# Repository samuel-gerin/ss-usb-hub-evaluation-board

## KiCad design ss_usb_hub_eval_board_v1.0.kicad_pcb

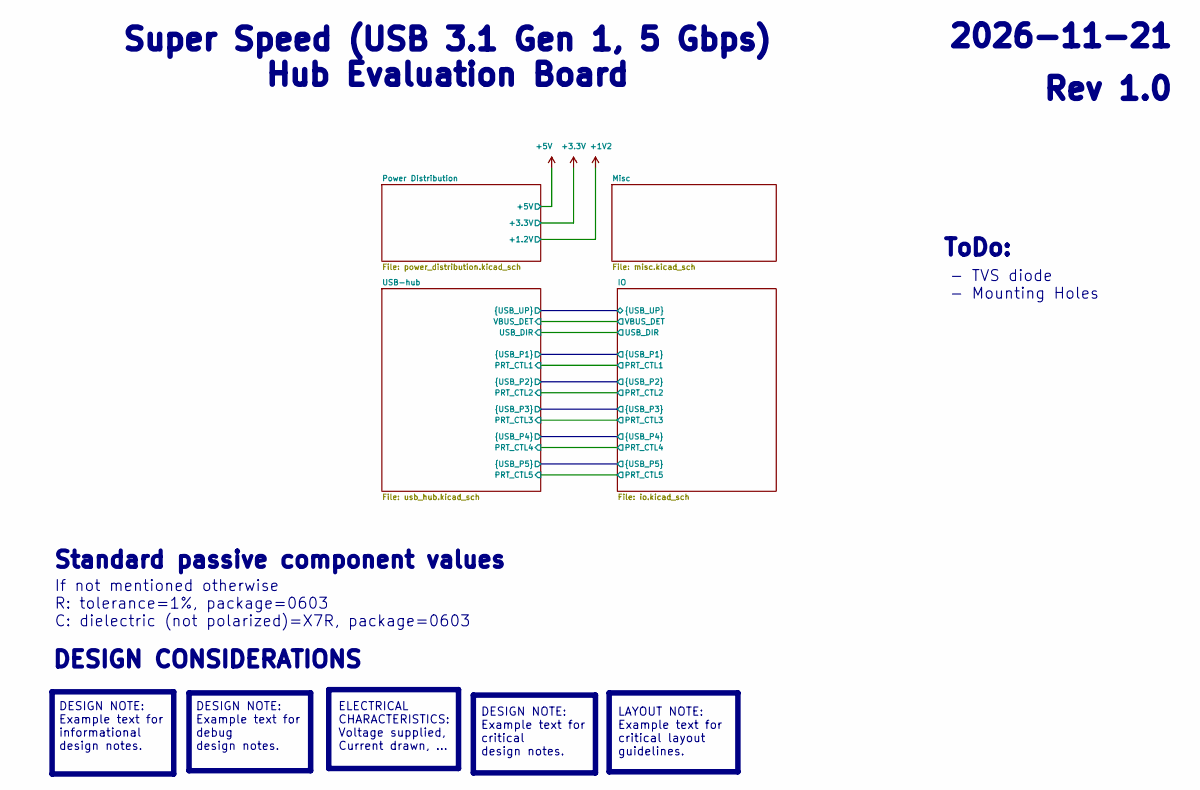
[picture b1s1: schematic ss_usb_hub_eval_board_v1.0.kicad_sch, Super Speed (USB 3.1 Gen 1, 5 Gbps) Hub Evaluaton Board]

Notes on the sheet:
If not mentioned otherwise R: tolerance=1%, package=0603 C: dielectric (not polarized)=X7R, package=0603
- TVS diode - Mounting Holes
DESIGN NOTE: Example text for critical design notes.
2026-11-21
Standard passive component values
Rev 1.0
DESIGN NOTE: Example text for informational design notes.
LAYOUT NOTE: Example text for critical layout guidelines.
DESIGN NOTE: Example text for debug design notes.
ELECTRICAL CHARACTERISTICS: Voltage supplied, Current drawn, ...
ToDo:
Super Speed (USB 3.1 Gen 1, 5 Gbps) Hub Evaluation Board
DESIGN CONSIDERATIONS

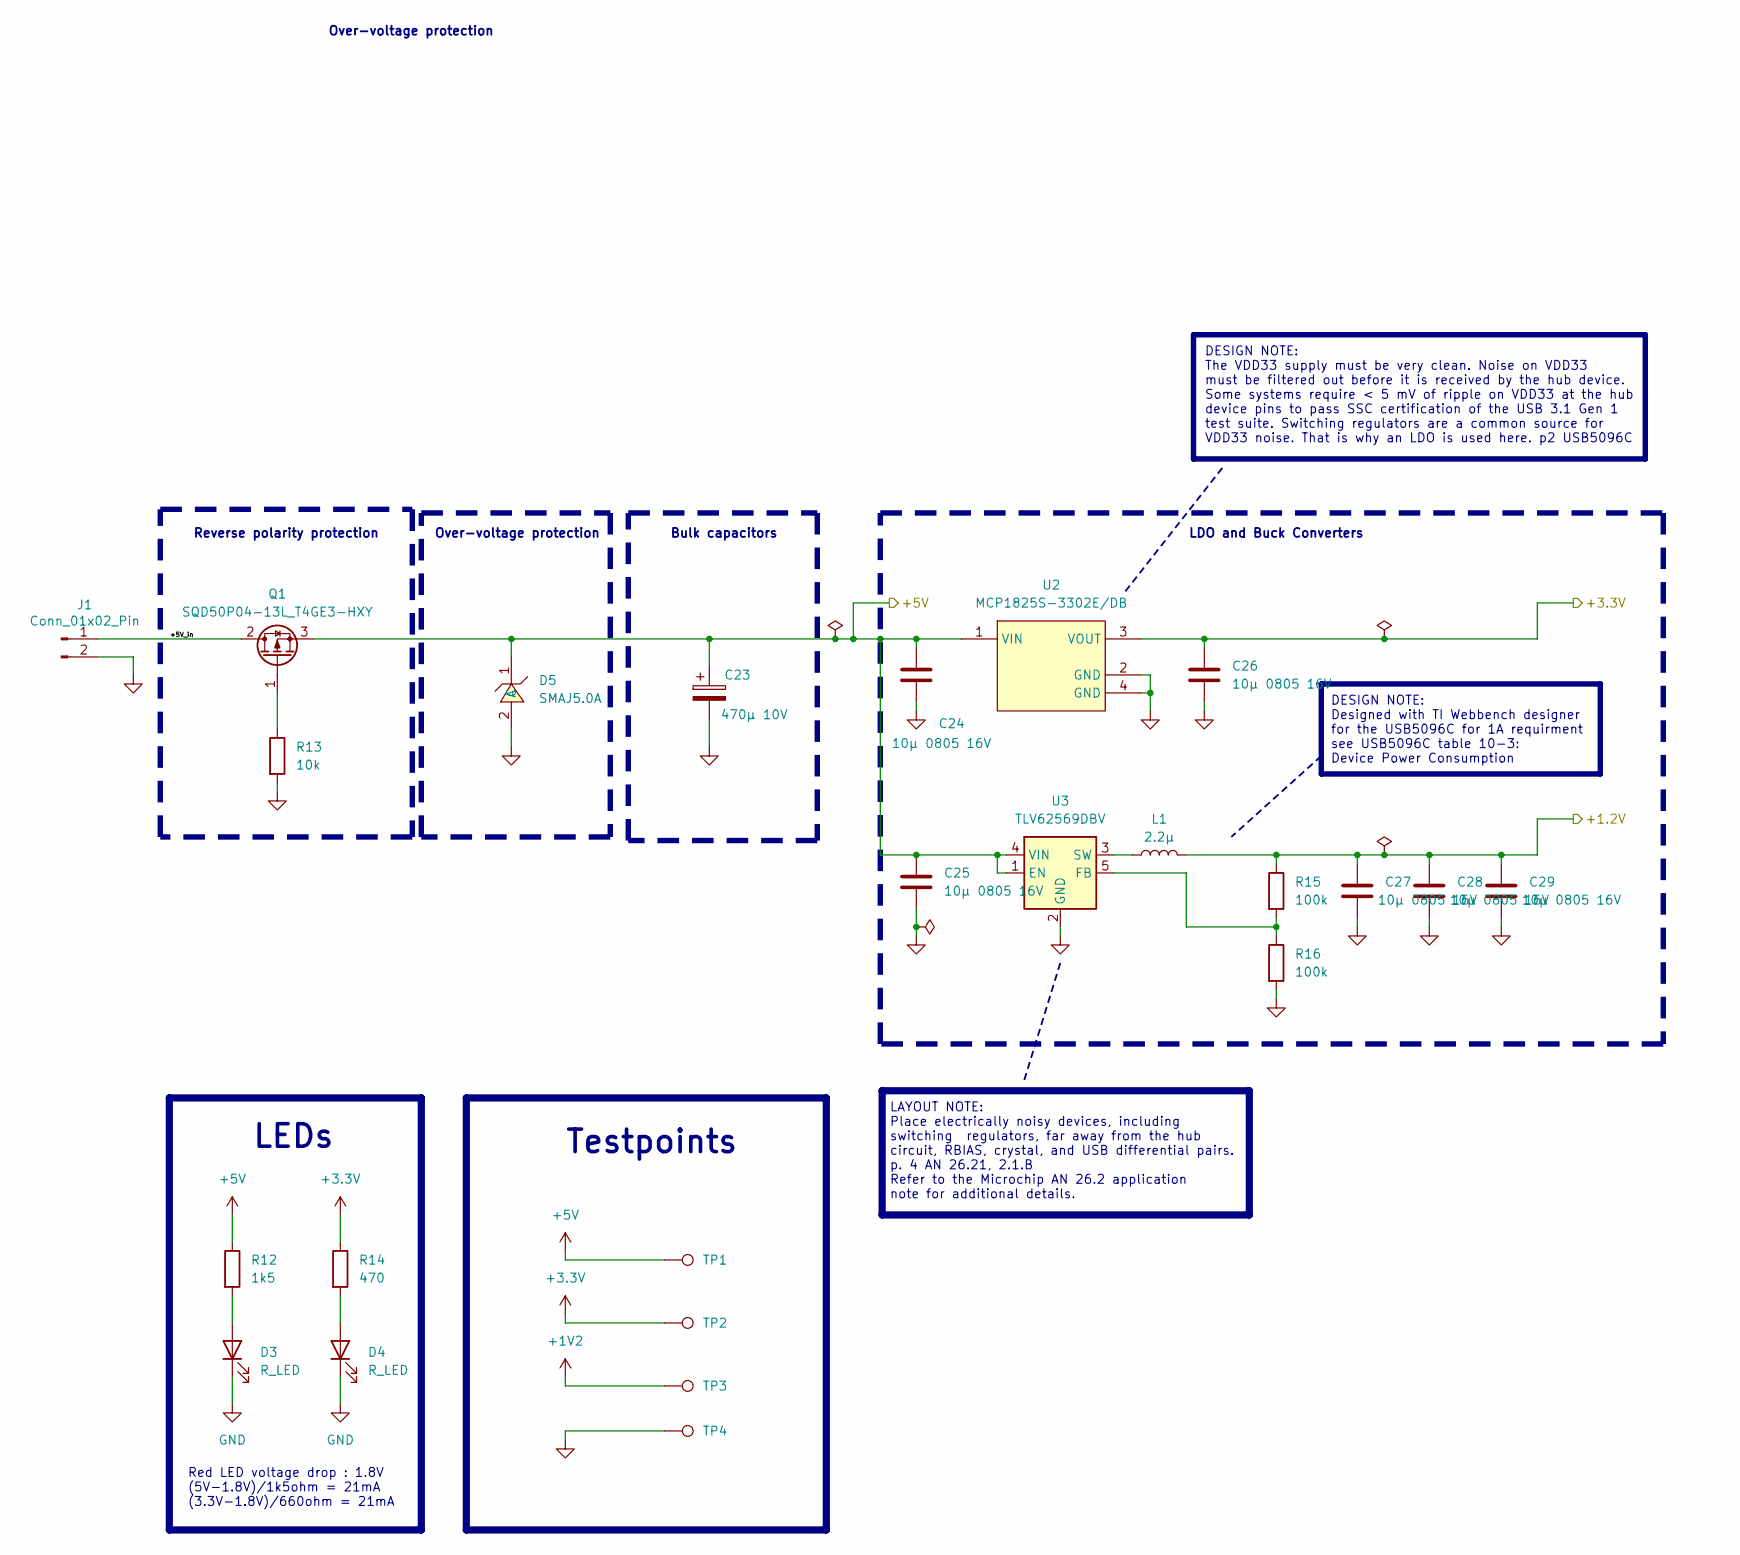
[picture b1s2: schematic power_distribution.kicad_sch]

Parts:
C23: 470µ 10V; CP_Elec_10x12.5; LCSC C22469994
C24, C25, C26, C27, C28, C29: 10µ 0805 16V; C_0805_2012Metric; LCSC C1713
D3, D4: R_LED; LED_0603_1608Metric; LCSC C2286
D5: SMAJ5.0A; SMA_L4.3-W2.6-LS5.2-RD; MPN SMAJ5.0A; LCSC Part C83329
J1: Conn_01x02_Pin; TerminalBlock_Phoenix_MKDS-1,5-2-5.08_1x02_P5.08mm_Horizont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
L1: 2.2µ; IND-SMD_L4.0-W4.0-A; LCSC C3151182
Q1: SQD50P04-13L_T4GE3-HXY; TO-252-2; LCSC C49256455
R12: 1k5; R_0603_1608Metric; LCSC C22843
R13: 10k; R_0805_2012Metric; LCSC C17414
R14: 470; R_0603_1608Metric; LCSC C23179
R15, R16: 100k; R_0603_1608Metric; LCSC C25803
TP1, TP2, TP3: TestPoint; TH_BD3.2-D2.0; LCSC C238122
TP4: TestPoint; TH_BD3.2-D2.0; LCSC C5199900
U2: MCP1825S-3302E/DB; SOT-223-3_L6.5-W3.4-P2.30-LS7.0-BR; MPN MCP1825S-3302E/DB; LCSC Part C148031
U3: TLV62569DBV; SOT-23-5; LCSC C141836

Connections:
+1V2: C27.1, C28.1, C29.1, L1.2, R15.1, TP3.1 (1_1); also elsewhere on the board
+3.3V: C26.1, R14.1, TP2.1 (1_1), U2.3 (VOUT); also elsewhere on the board
+5V: C23.1, C24.1, C25.1, D5.1 (C), Q1.3 (S), R12.1, TP1.1 (1_1), U2.1 (VIN), U3.1 (EN), U3.4 (VIN); also elsewhere on the board
/Power Distribution/+5V_in: J1.1, Q1.2 (D)
GND: C23.2, C24.2, C25.2, C26.2, C27.2, C28.2, C29.2, D3.1 (K), D4.1 (K), D5.2 (A), J1.2, R13.2, R16.2, TP4.1 (1_1), U2.2 (GND), U2.4 (GND), U3.2 (GND); also elsewhere on the board
unnamed: D3.2 (A), R12.2
unnamed: D4.2 (A), R14.2
unnamed: Q1.1 (G), R13.1
unnamed: R15.2, R16.1, U3.5 (FB)
unnamed: L1.1, U3.3 (SW)

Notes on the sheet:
Red LED voltage drop : 1.8V (5V-1.8V)/1k5ohm = 21mA (3.3V-1.8V)/660ohm = 21mA
Reverse polarity protection
LDO and Buck Converters
Over-voltage protection
Testpoints
Bulk capacitors
DESIGN NOTE: Designed with TI Webbench designer for the USB5096C for 1A requirment see USB5096C table 10-3: Device Power Consumption
LAYOUT NOTE: Place electrically noisy devices, including switching regulators, far away from the hub circuit, RBIAS, crystal, and USB differential pairs. p. 4 AN 26.21, 2.1.B Refer to the Microchip AN 26.2 application note for additional details.
DESIGN NOTE: The VDD33 supply must be very clean. Noise on VDD33 must be filtered out before it is received by the hub device. Some systems require < 5 mV of ripple on VDD33 at the hub device pins to pass SSC certification of the USB 3.1 Gen 1 test suite. Switching regulators are a common source fo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
LEDs

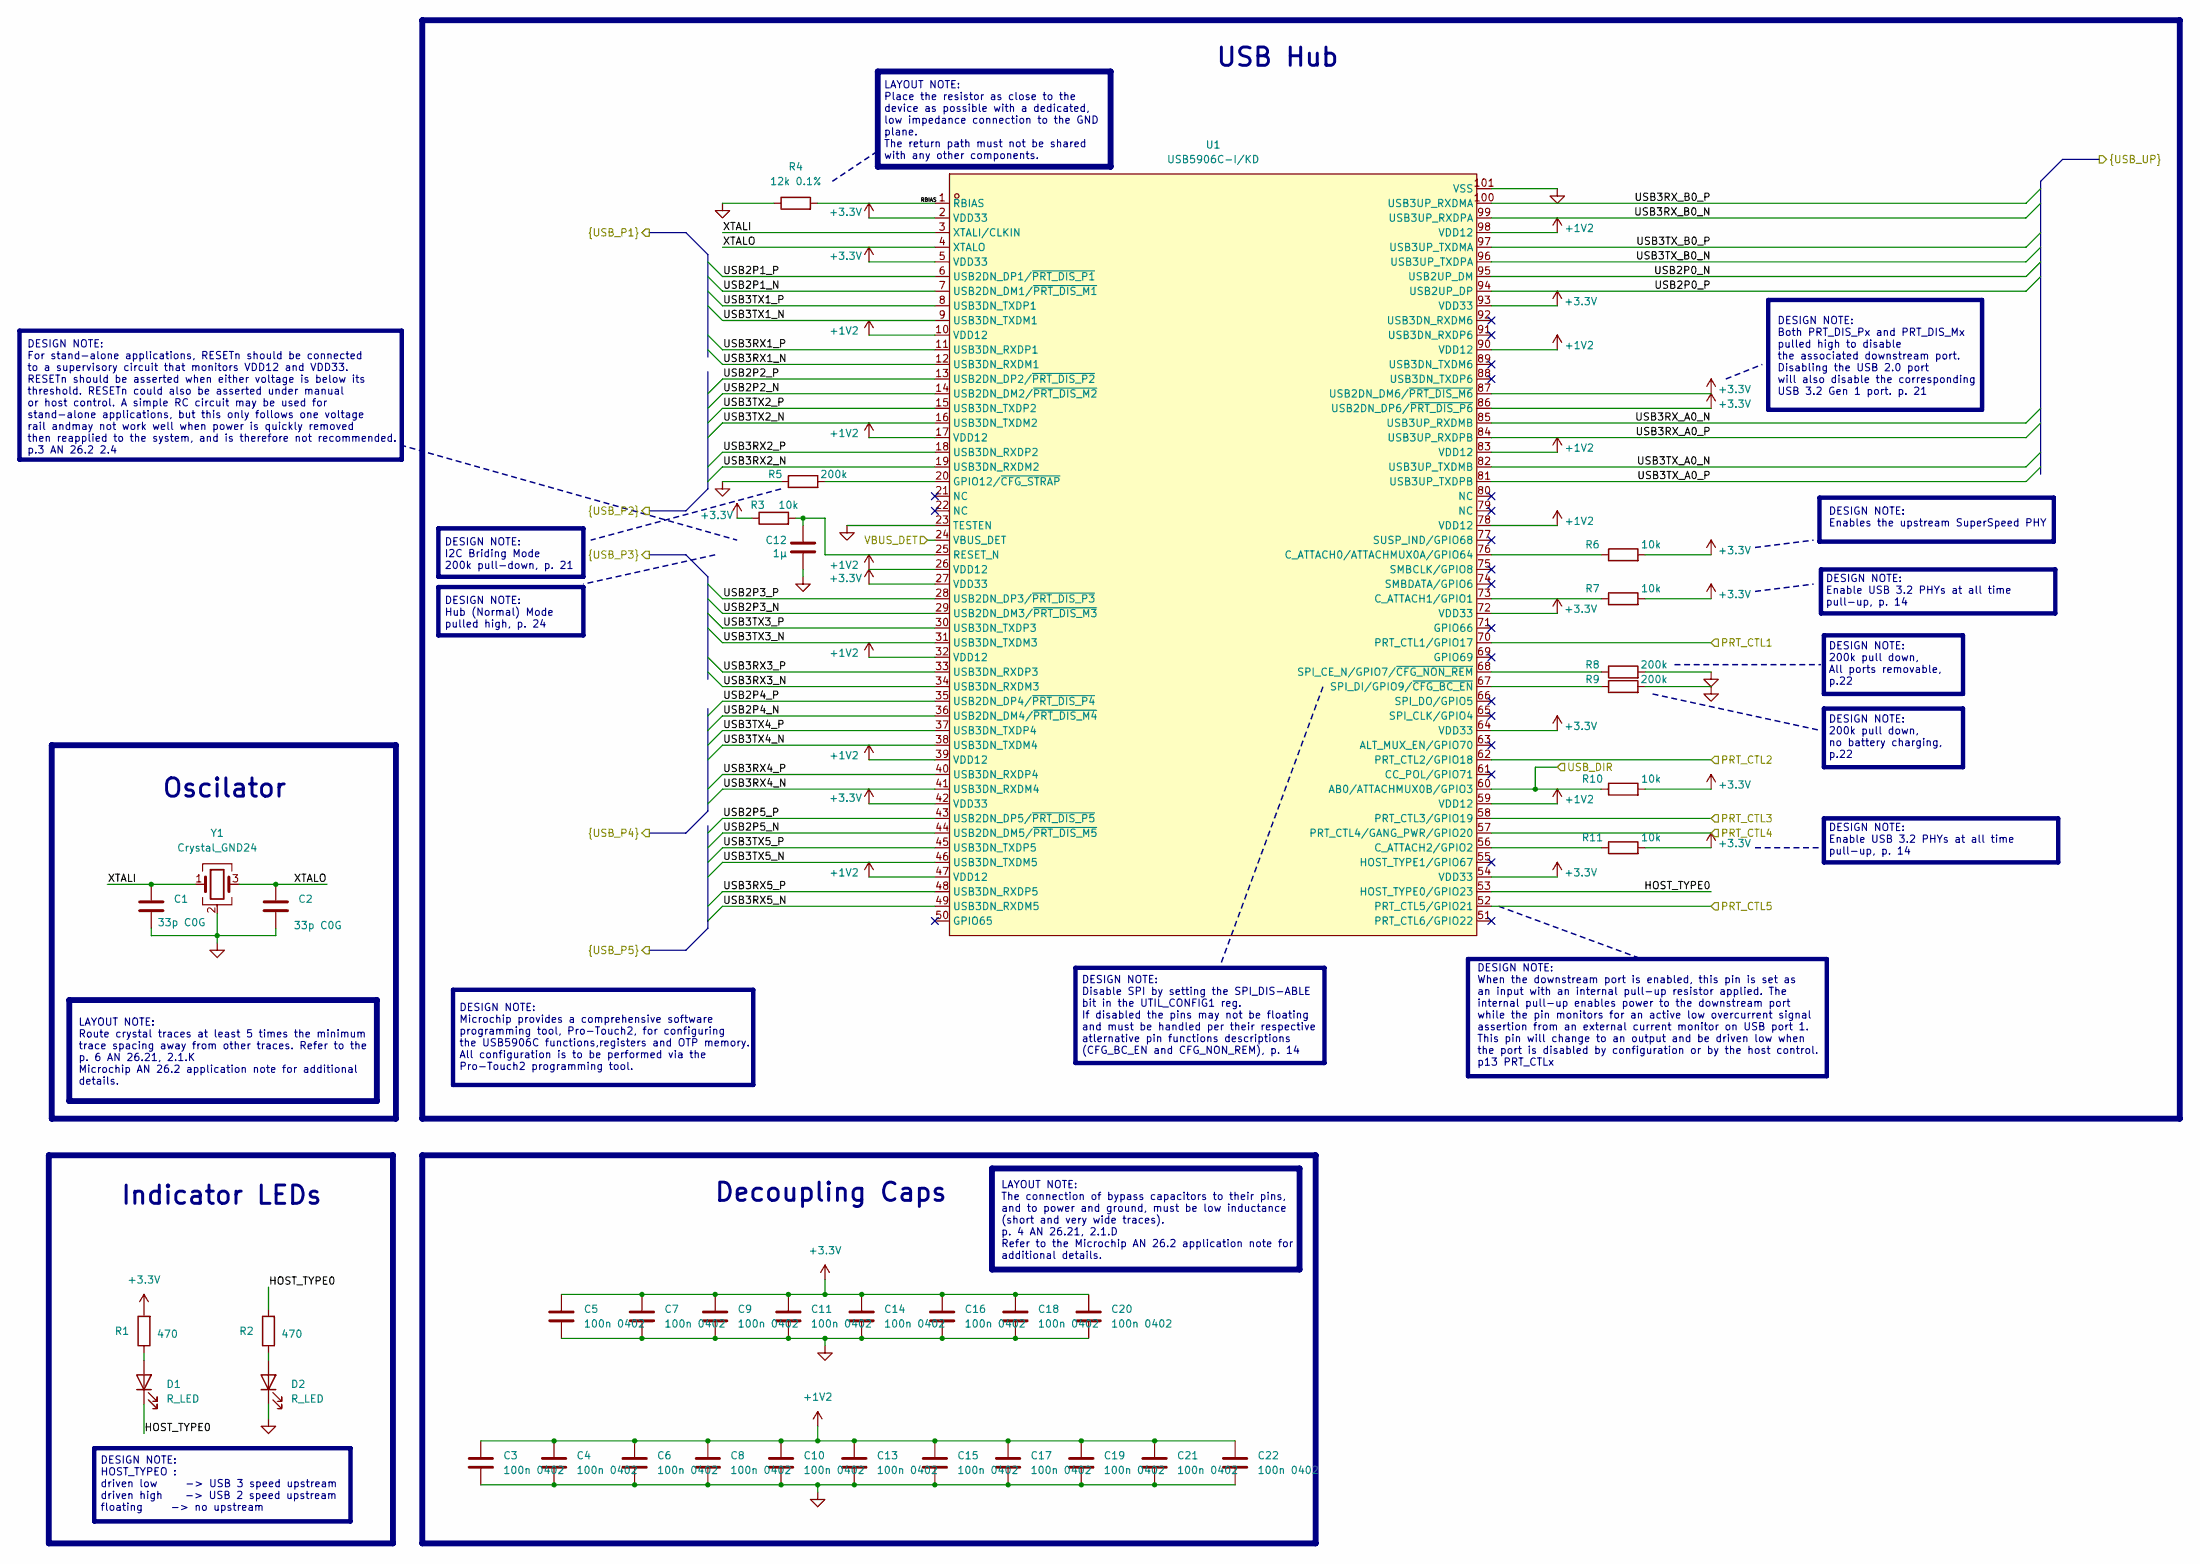
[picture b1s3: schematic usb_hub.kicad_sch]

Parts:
C1, C2: 33p C0G; C_0603_1608Metric; LCSC C1663
C3, C4, C5, C6, C7, C8, C9, C10, C11, C13, C14, C15, C16, C17, C18, C19, C20, C21, C22: 100n 0402; C_0402_1005Metric; LCSC C1525
C12: 1µ; C_0603_1608Metric; LCSC C15849
D1, D2: R_LED; LED_0603_1608Metric; LCSC C2286
R1, R2: 470; R_0603_1608Metric; LCSC C23179
R3, R6, R7, R10, R11: 10k; R_0603_1608Metric; LCSC C25804
R4: 12k 0.1%; R_0603_1608Metric; LCSC C326735
R5, R8, R9: 200k; R_0603_1608Metric; LCSC C25811
U1: USB5906C-I/KD; VQFN-100_L12.0-W12.0-P0.40-TL-EP8.0; MPN USB5906C-I/KD; LCSC Part C3210693
Y1: Crystal_GND24; CRYSTAL-SMD_4P-L3.2-W2.5-BL-2

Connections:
+1V2: C3.1, C4.1, C6.1, C8.1, C10.1, C13.1, C15.1, C17.1, C19.1, C21.1, C22.1, U1.10 (VDD12), U1.17 (VDD12), U1.26 (VDD12), U1.32 (VDD12), U1.39 (VDD12), U1.47 (VDD12), U1.59 (VDD12), U1.78 (VDD12), U1.83 (VDD12), U1.90 (VDD12), U1.98 (VDD12); also elsewhere on the board
+3.3V: C5.1, C7.1, C9.1, C11.1, C14.1, C16.1, C18.1, C20.1, R1.2, R3.1, R6.2, R7.2, R10.2, R11.2, U1.2 (VDD33), U1.5 (VDD33), U1.27 (VDD33), U1.42 (VDD33), U1.54 (VDD33), U1.64 (VDD33), U1.72 (VDD33), U1.86 (USB2DN_DP6/~PRT_DIS_P6), U1.87 (USB2DN_DM6/~PRT_DIS_M6), U1.93 (VDD33); also elsewhere on the board
/IO/PRT_CTL1: U1.70 (PRT_CTL1/GPIO17); also elsewhere on the board
/IO/PRT_CTL2: U1.62 (PRT_CTL2/GPIO18); also elsewhere on the board
/IO/PRT_CTL3: U1.58 (PRT_CTL3/GPIO19); also elsewhere on the board
/IO/PRT_CTL4: U1.57 (PRT_CTL4/GANG_PWR/GPIO20); also elsewhere on the board
/IO/PRT_CTL5: U1.52 (PRT_CTL5/GPIO21); also elsewhere on the board
/IO/USB2P0_N: U1.95 (USB2UP_DM); also elsewhere on the board
/IO/USB2P0_P: U1.94 (USB2UP_DP); also elsewhere on the board
/IO/USB2P1_N: U1.7 (USB2DN_DM1/~PRT_DIS_M1); also elsewhere on the board
/IO/USB2P1_P: U1.6 (USB2DN_DP1/~PRT_DIS_P1); also elsewhere on the board
/IO/USB2P2_N: U1.14 (USB2DN_DM2/~PRT_DIS_M2); also elsewhere on the board
/IO/USB2P2_P: U1.13 (USB2DN_DP2/~PRT_DIS_P2); also elsewhere on the board
/IO/USB2P3_N: U1.29 (USB2DN_DM3/~PRT_DIS_M3); also elsewhere on the board
/IO/USB2P3_P: U1.28 (USB2DN_DP3/~PRT_DIS_P3); also elsewhere on the board
/IO/USB2P4_N: U1.36 (USB2DN_DM4/~PRT_DIS_M4); also elsewhere on the board
/IO/USB2P4_P: U1.35 (USB2DN_DP4/~PRT_DIS_P4); also elsewhere on the board
/IO/USB2P5_N: U1.44 (USB2DN_DM5/~PRT_DIS_M5); also elsewhere on the board
/IO/USB2P5_P: U1.43 (USB2DN_DP5/~PRT_DIS_P5); also elsewhere on the board
/IO/USB3RX1_N: U1.12 (USB3DN_RXDM1); also elsewhere on the board
/IO/USB3RX1_P: U1.11 (USB3DN_RXDP1); also elsewhere on the board
/IO/USB3RX2_N: U1.19 (USB3DN_RXDM2); also elsewhere on the board
/IO/USB3RX2_P: U1.18 (USB3DN_RXDP2); also elsewhere on the board
/IO/USB3RX3_N: U1.34 (USB3DN_RXDM3); also elsewhere on the board
/IO/USB3RX3_P: U1.33 (USB3DN_RXDP3); also elsewhere on the board
/IO/USB3RX4_N: U1.41 (USB3DN_RXDM4); also elsewhere on the board
/IO/USB3RX4_P: U1.40 (USB3DN_RXDP4); also elsewhere on the board
/IO/USB3RX5_N: U1.49 (USB3DN_RXDM5); also elsewhere on the board
/IO/USB3RX5_P: U1.48 (USB3DN_RXDP5); also elsewhere on the board
/IO/USB3RX_A0_N: U1.85 (USB3UP_RXDMB); also elsewhere on the board
/IO/USB3RX_A0_P: U1.84 (USB3UP_RXDPB); also elsewhere on the board
/IO/USB3RX_B0_N: U1.99 (USB3UP_RXDPA); also elsewhere on the board
/IO/USB3RX_B0_P: U1.100 (USB3UP_RXDMA); also elsewhere on the board
/IO/USB3TX1_N: U1.9 (USB3DN_TXDM1); also elsewhere on the board
/IO/USB3TX1_P: U1.8 (USB3DN_TXDP1); also elsewhere on the board
/IO/USB3TX2_N: U1.16 (USB3DN_TXDM2); also elsewhere on the board
/IO/USB3TX2_P: U1.15 (USB3DN_TXDP2); also elsewhere on the board
/IO/USB3TX3_N: U1.31 (USB3DN_TXDM3); also elsewhere on the board
/IO/USB3TX3_P: U1.30 (USB3DN_TXDP3); also elsewhere on the board
/IO/USB3TX4_N: U1.38 (USB3DN_TXDM4); also elsewhere on the board
/IO/USB3TX4_P: U1.37 (USB3DN_TXDP4); also elsewhere on the board
/IO/USB3TX5_N: U1.46 (USB3DN_TXDM5); also elsewhere on the board
/IO/USB3TX5_P: U1.45 (USB3DN_TXDP5); also elsewhere on the board
/IO/USB3TX_A0_N: U1.82 (USB3UP_TXDMB); also elsewhere on the board
/IO/USB3TX_A0_P: U1.81 (USB3UP_TXDPB); also elsewhere on the board
/IO/USB3TX_B0_N: U1.96 (USB3UP_TXDPA); also elsewhere on the board
/IO/USB3TX_B0_P: U1.97 (USB3UP_TXDMA); also elsewhere on the board
/IO/USB_DIR: R10.1, U1.60 (AB0/ATTACHMUX0B/GPIO3); also elsewhere on the board
/IO/VBUS_DET: U1.24 (VBUS_DET); also elsewhere on the board
/USB-hub/HOST_TYPE0: D1.1 (K), R2.2, U1.53 (HOST_TYPE0/GPIO23)
/USB-hub/RBIAS: R4.2, U1.1 (RBIAS)
/USB-hub/XTALI: C1.1, U1.3 (XTALI/CLKIN), Y1.1
/USB-hub/XTALO: C2.1, U1.4 (XTALO), Y1.3
GND: C1.2, C2.2, C3.2, C4.2, C5.2, C6.2, C7.2, C8.2, C9.2, C10.2, C11.2, C12.2, C13.2, C14.2, C15.2, C16.2, C17.2, C18.2, C19.2, C20.2, C21.2, C22.2, D2.1 (K), R4.1, R5.1, R8.2, R9.2, U1.23 (TESTEN), U1.101 (VSS), Y1.2 (G), Y1.4 (G); also elsewhere on the board
unnamed: D1.2 (A), R1.1
unnamed: D2.2 (A), R2.1
unnamed: R6.1, U1.76 (C_ATTACH0/ATTACHMUX0A/GPIO64)
unnamed: R7.1, U1.73 (C_ATTACH1/GPIO1)
unnamed: R11.1, U1.56 (C_ATTACH2/GPIO2)
unnamed: R5.2, U1.20 (GPIO12/~CFG_STRAP)
unnamed: C12.1, R3.2, U1.25 (RESET_N)
unnamed: R8.1, U1.68 (SPI_CE_N/GPIO7/~CFG_NON_REM)
unnamed: R9.1, U1.67 (SPI_DI/GPIO9/~CFG_BC_EN)

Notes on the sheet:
LAYOUT NOTE: The connection of bypass capacitors to their pins, and to power and ground, must be low inductance (short and very wide traces). p. 4 AN 26.21, 2.1.D Refer to the Microchip AN 26.2 application note for additional details.
DESIGN NOTE: Both PRT_DIS_Px and PRT_DIS_Mx pulled high to disable the associated downstream port. Disabling the USB 2.0 port will also disable the corresponding USB 3.2 Gen 1 port. p. 21
DESIGN NOTE: For stand-alone applications, RESETn should be connected to a supervisory circuit that monitors VDD12 and VDD33. RESETn should be asserted when either voltage is below its threshold. RESETn could also be asserted under manual or host control. A simple RC circuit may be used for stand-a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
USB Hub
DESIGN NOTE: HOST_TYPEO : driven low -> USB 3 speed upstream driven high -> USB 2 speed upstream floating -> no upstream
DESIGN NOTE: 200k pull down, All ports removable, p.22
LAYOUT NOTE: Route crystal traces at least 5 times the minimum trace spacing away from other traces. Refer to the p. 6 AN 26.21, 2.1.K Microchip AN 26.2 application note for additional details.
DESIGN NOTE: 200k pull down, no battery charging, p.22
Oscilator
DESIGN NOTE: Microchip provides a comprehensive software programming tool, Pro-Touch2, for configuring the USB5906C functions,registers and OTP memory. All configuration is to be performed via the Pro-Touch2 programming tool.
LAYOUT NOTE: Place the resistor as close to the device as possible with a dedicated, low impedance connection to the GND plane. The return path must not be shared with any other components.
DESIGN NOTE: Enables the upstream SuperSpeed PHY
Indicator LEDs
DESIGN NOTE: I2C Briding Mode 200k pull-down, p. 21
DESIGN NOTE: Hub (Normal) Mode pulled high, p. 24
DESIGN NOTE: Enable USB 3.2 PHYs at all time pull-up, p. 14
DESIGN NOTE: When the downstream port is enabled, this pin is set as an input with an internal pull-up resistor applied. The internal pull-up enables power to the downstream port while the pin monitors for an active low overcurrent signal assertion from an external current monitor on USB port 1. Th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
DESIGN NOTE: Disable SPI by setting the SPI_DIS-ABLE bit in the UTIL_CONFIG1 reg. If disabled the pins may not be floating and must be handled per their respective atlernative pin functions descriptions (CFG_BC_EN and CFG_NON_REM), p. 14
Decoupling Caps

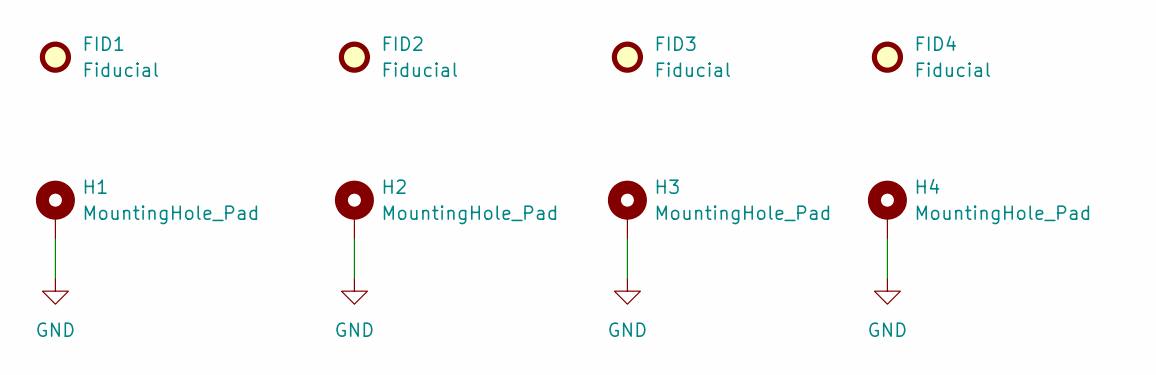
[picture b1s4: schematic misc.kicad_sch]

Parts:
FID1, FID2, FID3, FID4: Fiducial; Fiducial_0.5mm_Mask2mm
H1, H2, H3, H4: MountingHole_Pad; MountingHole_2.2mm_M2_Pad_Via

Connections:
GND: H1.1 (1_1), H2.1 (1_1), H3.1 (1_1), H4.1 (1_1); also elsewhere on the board
